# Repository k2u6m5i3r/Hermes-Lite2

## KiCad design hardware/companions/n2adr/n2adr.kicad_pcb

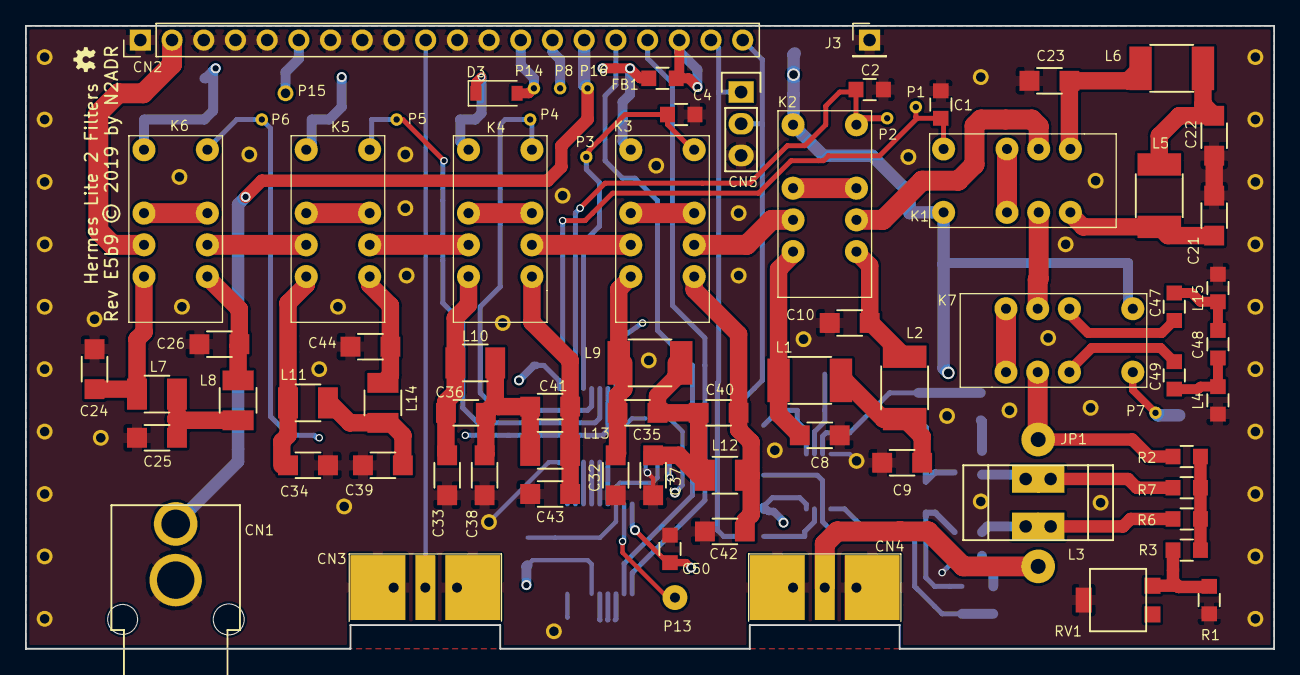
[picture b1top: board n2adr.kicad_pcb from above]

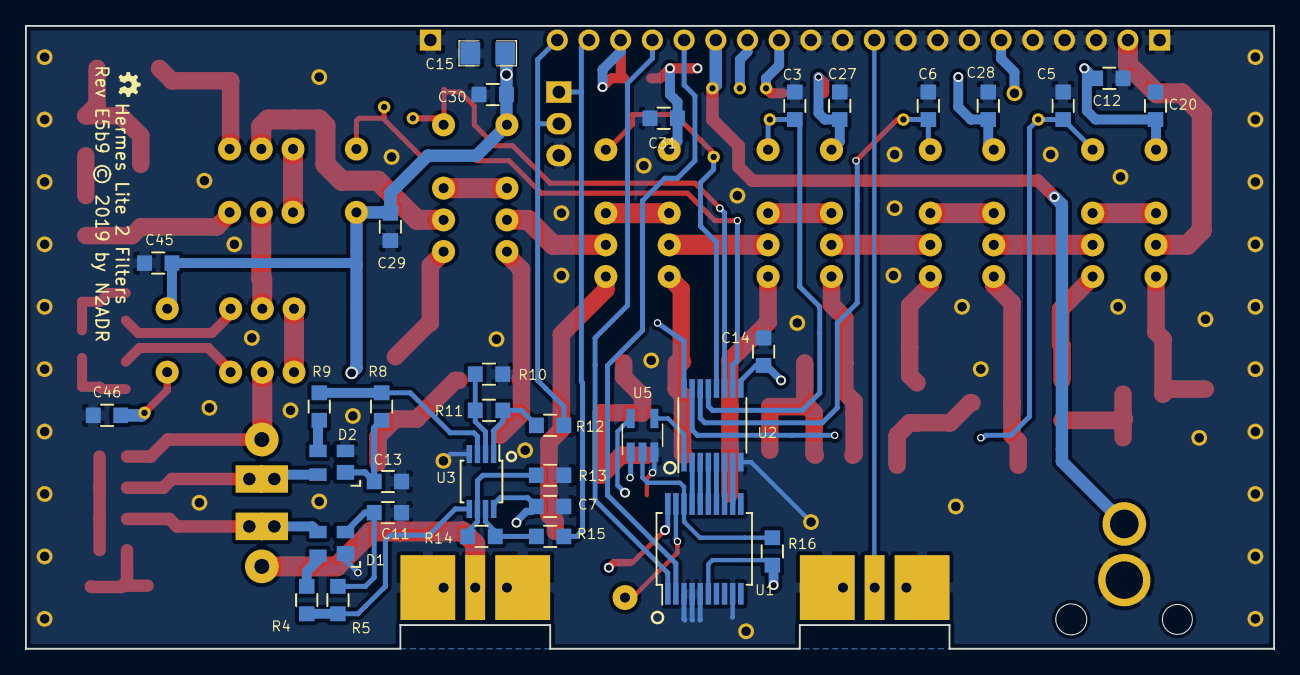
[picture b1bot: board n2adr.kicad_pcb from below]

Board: 4 copper layers, 100.0 x 49.9 mm, 112 parts (34 on the bottom side), 80 nets.

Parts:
C1, C2, C3, C4, C5, C6, C7, C11, C13, C14, C20, C27, C28, C29, C30, C31, C45, C46, C50: 100n; SMD_0805
C8, C10: 1000p; SMD_1206
C9, C21, C23: 1800p; SMD_1206
C12: 22uF; SMD_0805
C15: 100uF; SMD-1206
C22: 3300p; SMD_1206
C24, C26, C33: 150p; SMD_1206
C25, C39: 330p; SMD_1206
C32, C38, C40: 270p; SMD_1206
C34, C44: 180p; SMD_1206
C35: 100p; SMD_1206
C36: 39p; SMD_1206
C37: 560p; SMD_1206
C41, C42: 220p; SMD_1206
C43: 68p; SMD_1206
C47, C49: 1500p; SMD_0805
C48: 680p; SMD_0805
CN1: Audio-Jack-2; PhonoRcaRCJ-04x
CN2: Conn_01x20; Pin_Header_Straight_1x20_Pitch2.54mm
CN3, CN4: SMA; BNCEDGE
CN5: CONN_01X03; Pin_Header_Straight_1x03
D1, D2: BAS40-07; SOT-143
D3: 1N4148; D_SOD-123
FB1: FB; SMD_0805
J3: Conn_01x01; Pin_Header_Straight_1x01_Pitch2.54mm
JP1: 1T; WireConnection_1.20mmDrill
K1, K2, K3, K4, K5, K6, K7: EC2-3NU; RelayDPDT01
L1, L2: 1.8u; SMD_1812
L3: 10T; ToroidT37
L4, L15: 1.8u; SMD_0805
L5, L6: 3.9u; SMD_1812
L7, L8: 220n; SMD_1210
L9: 1000n; SMD_1812
L10: 560n; SMD_1210
L11, L14: 390n; SMD_1210
L12: 680n; SMD_1210
L13: 270n; SMD_1210
P1, P2, P3, P4, P5, P6, P7, P8, P14, P16: TST; WirePad_0.5mm
P13, P15: TST; SolderWirePad_single_0-8mmDrill
R1: 22 1%; SMD_0805
R2, R10, R13: 2K2 1%; SMD_0805
R3: 56 1%; SMD_0805
R4, R5, R8, R9: 4K7; SMD_0805
R6, R7: 18 1%; SMD_0805
R11, R14: 6K2 1%; SMD_0805
R12, R15: 330; SMD_0805
R16: DNI; SMD_0805
RV1: DNI; Trimpot_Bourns_3314G
U1: MCP23008; SSOP-20_5.3x7.2mm_Pitch0.65mm
U2: ULN2003LV; TSSOP-16_4.4x5mm_Pitch0.65mm
U3: AD8692; MSOP-8_3x3mm_Pitch0.65mm
U5: 74LVC1G00; SOT-23-5_HandSoldering

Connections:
+3V3: C7.2, C12.2, C14.2, C15.2, C20.2, C27.2, C28.2, C29.2, C30.2, C31.2, C45.2, C50.2, D3.1, FB1.1, K1.1, K2.1, K3.1, K4.1, K5.1, K6.1, K7.1, R16.1, U1.6, U1.20, U2.9, U3.8, U5.5
Band1: C1.2, K1.8, P1.1, U2.10
Band2: C2.2, K2.8, P2.1, U2.11
Band3: C4.2, K3.8, P3.1, U2.12
Band4: C3.2, K4.8, P4.1, U2.13
Band5: C6.2, K5.8, P5.1, U2.14
Band6: C5.2, K6.8, P6.1, U2.15
Band7: C46.2, K7.8, P7.1, U2.16
FilterOut: JP1.2, K7.6, R2.2
GND: C1.1, C2.1, C3.1, C4.1, C5.1, C6.1, C7.1, C8.1, C9.1, C10.1, C11.2, C12.1, C13.2, C14.1, C15.1, C20.1, C21.2, C22.2, C23.2, C24.1, C25.1, C26.1, C27.1, C28.1, C29.1, C30.1, C31.1, C32.1, C33.1, C34.1, C37.1, C38.1, C39.1, C42.1, C43.1, C44.1, C45.1, C46.1, C50.1, CN1.2, CN2.1, CN2.3, CN2.4, CN2.5, CN2.7, CN2.8, CN2.9, CN2.11, CN2.12, CN3.2, CN4.2, CN5.3, D1.1, D2.2, J3.1, L4.1, L15.1, R1.1, R10.1, R13.1, RV1.2, U1.3, U1.4, U1.5, U1.9, U2.8, U3.4, U5.3
INTTR: CN2.13, D3.2, P14.1, U5.1
unnamed: C8.2, K2.4, L1.1
unnamed: C9.2, L1.2, L2.1
unnamed: C10.2, K2.5, L2.2
unnamed: C11.1, D1.2, R5.2
unnamed: C13.1, D2.1, R8.2
unnamed: C21.1, K1.4, L5.1
unnamed: C22.1, L5.2, L6.1
unnamed: C23.1, K1.5, L6.2
unnamed: C24.2, K6.4, L7.1
unnamed: C25.2, L7.2, L8.1
unnamed: C26.2, K6.5, L8.2
unnamed: C32.2, C35.2, K3.4, L9.1
unnamed: C33.2, C36.2, K4.4, L10.1
unnamed: C34.2, K5.4, L11.1
unnamed: C35.1, C37.2, C40.2, L9.2, L12.1
unnamed: C36.1, C38.2, C41.2, L10.2, L13.1
unnamed: C39.2, L11.2, L14.1
unnamed: C40.1, C42.2, K3.5, L12.2
unnamed: C41.1, C43.2, K4.5, L13.2
unnamed: C44.2, K5.5, L14.2
unnamed: C47.1, C48.2, L15.2
unnamed: C47.2, K7.2
unnamed: C48.1, C49.2, L4.2
unnamed: C49.1, K7.7
unnamed: CN1.1, CN2.15, P16.1
unnamed: CN2.6, P15.1
unnamed: CN2.10, CN3.1
unnamed: CN2.14, P8.1
unnamed: CN2.16, U1.2
unnamed: CN2.17, U1.1
unnamed: CN2.18, FB1.2
unnamed: CN2.19, CN5.1, R15.2
unnamed: CN2.20, CN5.2, R12.2
unnamed: CN4.1, JP1.1
unnamed: D1.3, L3.1, R6.2
unnamed: D1.4, R4.2
unnamed: D2.3, R9.1
unnamed: D2.4, L3.2, R7.1
unnamed: K1.2, K1.7
unnamed: K1.3, K7.3
unnamed: K1.6, K2.6
unnamed: K2.2, K2.7
unnamed: K2.3, K3.6
unnamed: K3.2, K3.7
unnamed: K3.3, K4.6
unnamed: K4.2, K4.7
unnamed: K4.3, K5.6
unnamed: K5.2, K5.7
unnamed: K5.3, K6.6
unnamed: K6.2, K6.7
unnamed: K7.4, K7.5
unnamed: P13.1, U1.19
unnamed: R1.2, R3.1, RV1.1
unnamed: R2.1, R3.2, R6.1, R7.2
unnamed: R4.1, R5.1, U3.5
unnamed: R8.1, R9.2, U3.3
unnamed: R10.2, R11.1, U3.2
unnamed: R11.2, R12.1, U3.1
unnamed: R13.2, R14.1, U3.6
unnamed: R14.2, R15.1, U3.7
unnamed: R16.2, U1.18, U5.2
unnamed: U1.12, U2.7
unnamed: U1.13, U2.6
unnamed: U1.14, U2.5
unnamed: U1.15, U2.4
unnamed: U1.16, U2.3
unnamed: U1.17, U2.2
unnamed: U2.1, U5.4
RFInput: CN2.2, K6.3

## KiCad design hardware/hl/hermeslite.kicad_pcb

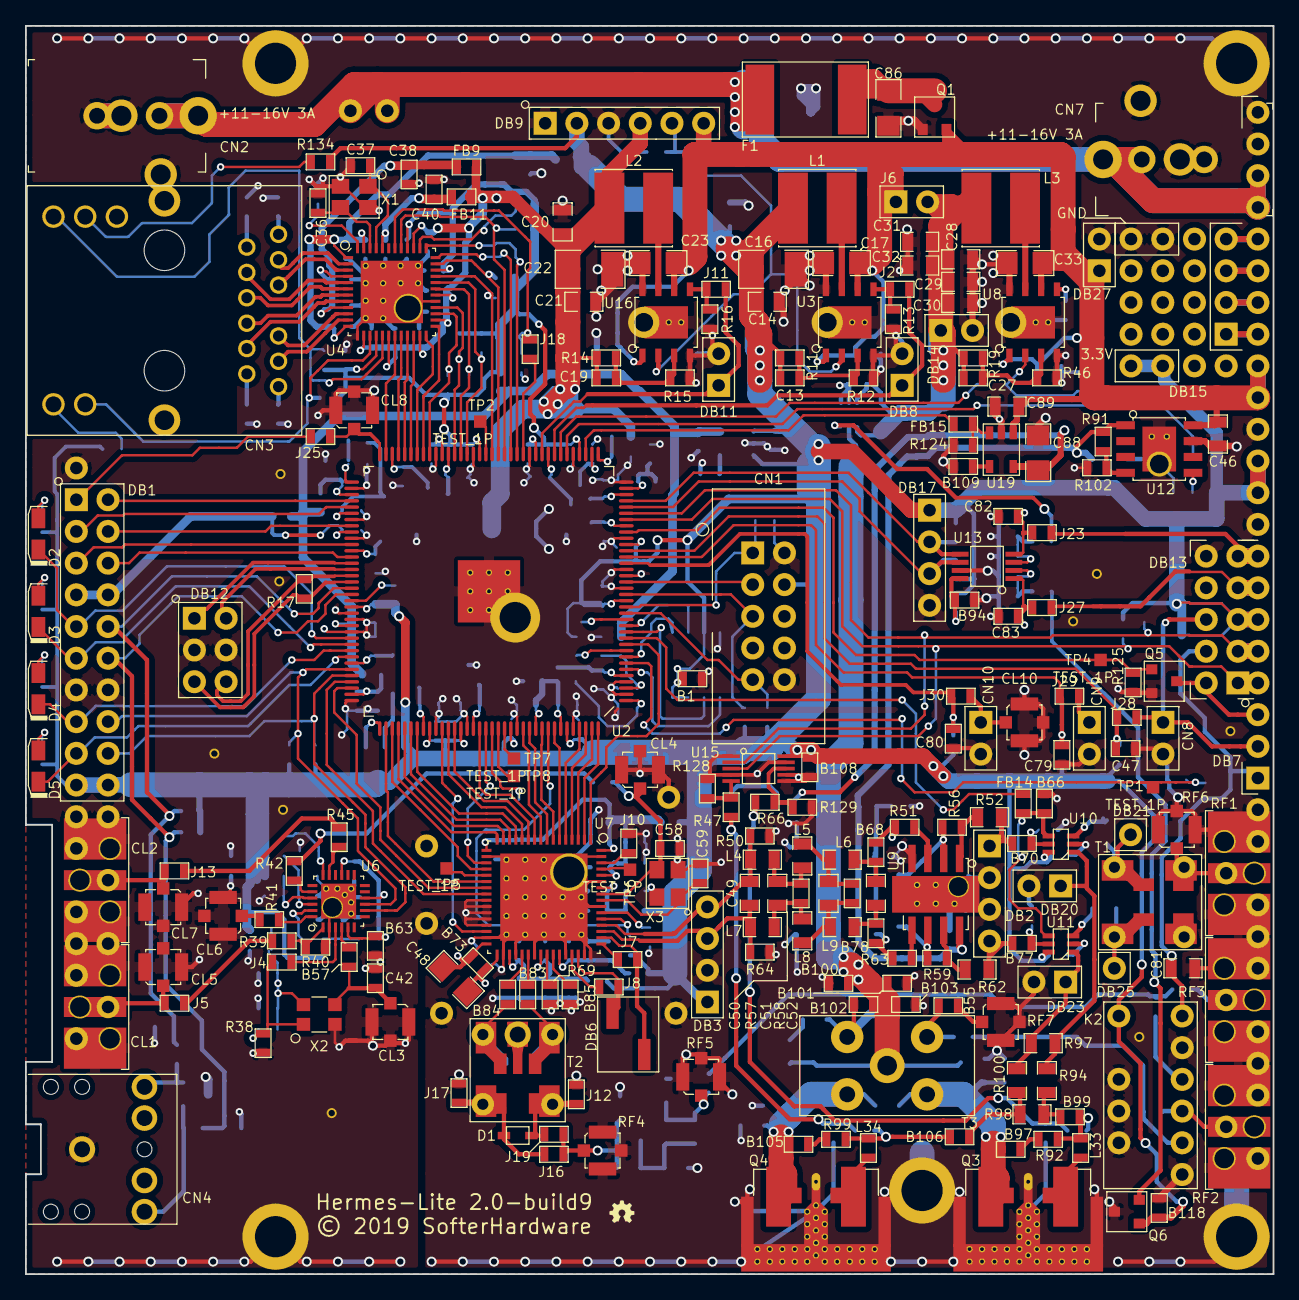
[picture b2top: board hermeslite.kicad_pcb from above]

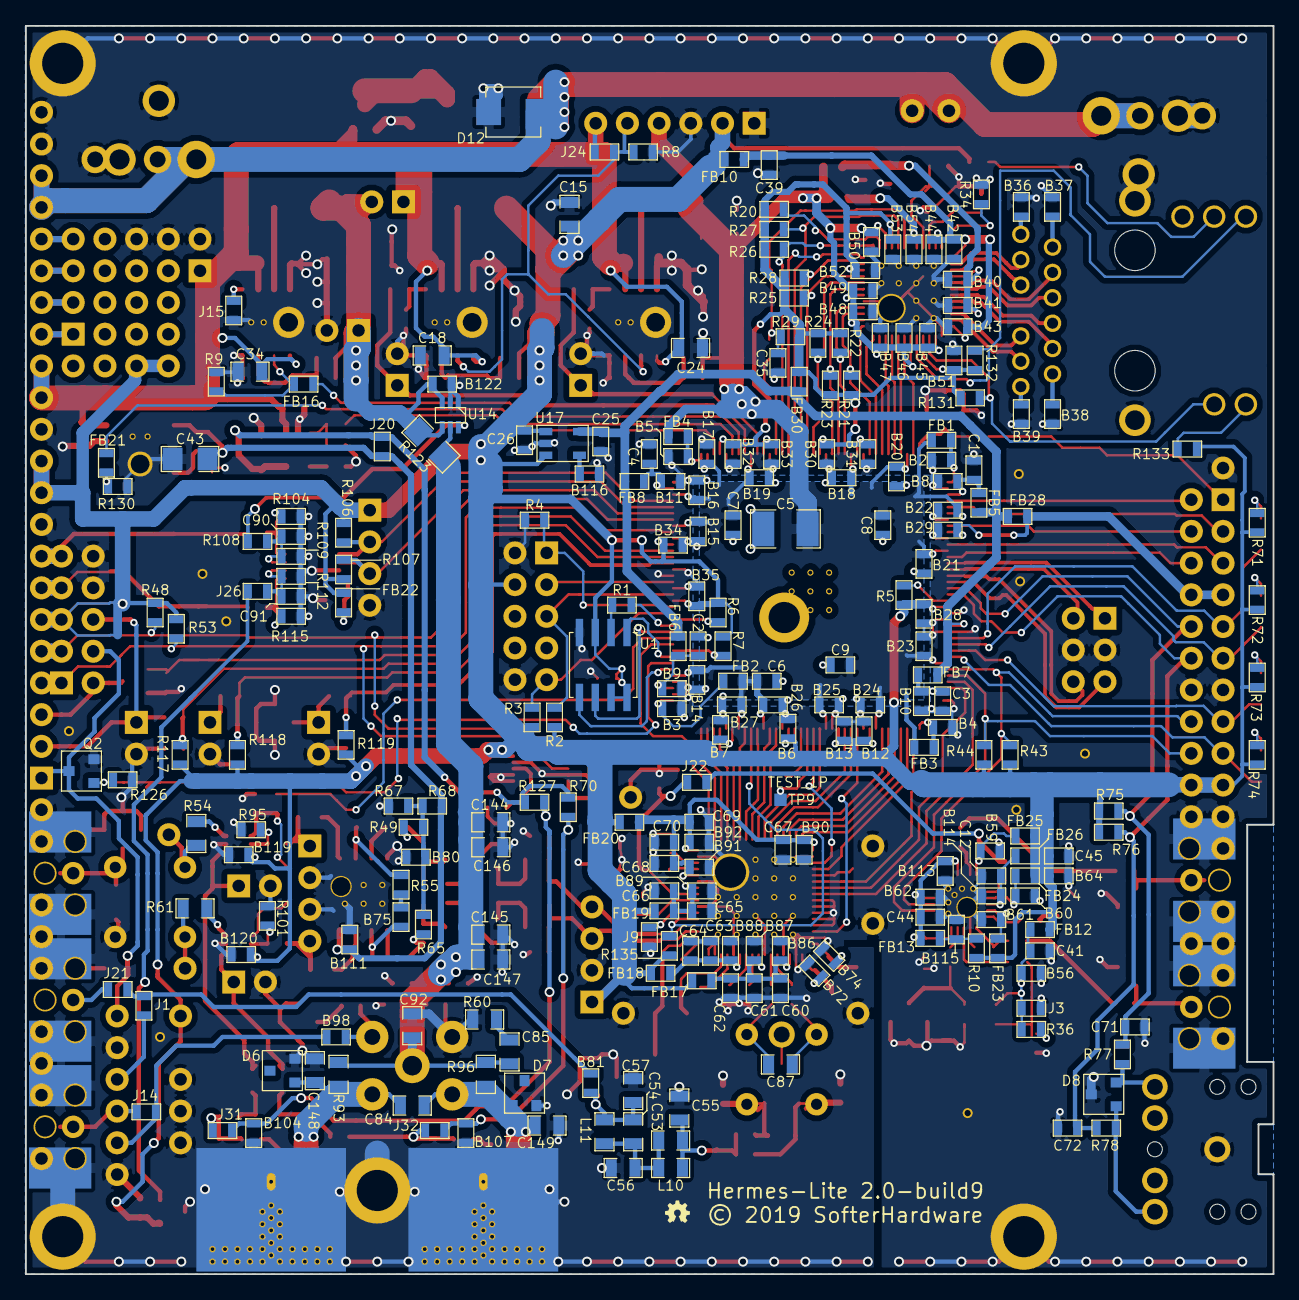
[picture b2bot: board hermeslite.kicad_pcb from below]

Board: 4 copper layers, 99.9 x 100.0 mm, 488 parts (246 on the bottom side), 274 nets.

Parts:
B1, B2, B3, B4, B5, B6, B7, B8, B9, B10, B11, B12, B13, B14, B15, B16, B17, B18, B19, B20, B21, B22, B23, B24, B25, B26, B27, B28, B29, B30, B31, B32, B33, B34, B35, B36, B37, B38, B39, B40, B41, B42, B43, B44, B45, B46, B47, B48, B49, B50, B51, B52, B53, B54, B55, B56, B57, B59, B60, B61, B62, B63, B64, B66, B68, B70, B72, B73, B74, B75, B77, B78, B80, B81, B83, B84, B85, B86, B87, B88, B89, B90, B91, B92, B94, B97, B98, B99, B100, B101, B102, B103, B104, B105, B106, B107, B108, B109, B111, B113, B114, B115, B116, B118, B119, B120, B122: 0.1uF; SMD-0603
C1, C2, C3, C4, C6, C7, C8, C9, C12, C25, C35, C38, C39, C40, C41, C44, C45, C62, C64, C66, C70: 10uF; SMD-0603
C5, C16, C22: 100uF; SMD-1210
C13, C19, C27, C82, C83, C90, C91: 4.7nF; SMD-0603
C14, C15, C20, C21, C28, C29, C30, C31, C32, C92: 22uF; SMD-0805
C17, C23, C33, C43, C48, C86, C88: 10uF; SMD-1206
C18, C24, C34: 4.7uF; SMD-0805
C26, C47, C60, C61, C63, C65, C67, C68, C69, C71, C72, C79, C80: 1uF; SMD-0603
C36, C37, C58, C59: 15pF; SMD-0603
C42: DNI; SMD-0603
C46, C89, C144, C145, C146, C147: 1uF; SMD-0805
C49: 75pF; SMD-0805
C50: 150pF; SMD-0805
C51: 160pF; SMD-0805
C52, C57, C81: 100pF; SMD-0805
C53, C54, C55: 10pF; SMD-0805
C56: 180pF; SMD-0805
C84: 390pF; SMD-0805
C85, C148, C149: 270pF; SMD-0805
C87: 8.2pF; SMD-0805
CL1, CL2: SMA; SMAEDGE_TH_L
CL3, CL4, CL5, CL6, CL7, CL8, CL10: uFL; UFL
CN1: USBBlaster2; USBBLASTER
CN2, CN7: PS; PWRBARREL2
CN3: MagJack; MAGJACK
CN4: STEREO
CN8, CN9, CN10: RFD2b; 2x1
D1: TVS; SOD323
D2, D3, D4, D5: Led_Small; LEDn
D6, D7: DNI; SOT23_3
D8: SM05; SOT23_3
D12: SMBJ18CA; smbj18ca
DB1: IO20; 10x2
DB2, DB3: RFD4d; 4x1
DB6: RFD2b; 2x1smt
DB7: IO22; 22x1
DB8, DB11, DB14, DB20, DB23, DB27: RFD2b; 2x1
DB9: IO6b; 6x1
DB12: IO6b; 3x2
DB13: IO10; 5x2
DB15: IO6b; 4x5
DB17: RFD4b; 4x1
DB21, DB25: DNI; 1x1
F1: 3A@20V; FUSE
FB1, FB2, FB3, FB4, FB5, FB6, FB7, FB8, FB9, FB10, FB11, FB12, FB13, FB14, FB15, FB16, FB17, FB18, FB19, FB20, FB21, FB22, FB23, FB24, FB25, FB26, FB28, FB30: FB; SMD-0603
GT1, GT2, GT3, GT4, GT10, GT11, GT12, GT13, GT14: DNI; GNDTAP
GT5, GT6, GT7, GT8, GT9: DNI; m1d1
J1, J2, J5, J9, J10, J11, J13, J14, J15, J17, J18, J19, J21, J22, J23, J24, J25, J26, J27, J28, J29, J30, J31, J32: JNC; SMD-0603
J3, J4, J7, J8, J12, J16, J20: JNO; SMD-0603
J6: RFD2b; 2x1
K2: NA3WK-K; DPDT_GND
L1, L3: 3.3uH; GENERICPSL
L2: 2.2uH; GENERICPSL
L4, L7: 240nH; SMD-0805
L5, L6, L8, L9: 270nH; SMD-0805
L10, L11: 330nH; SMD-0805
L33, L34: 0nH; SMD-0603
MH1, MH2, MH3, MH4, MH5: DNI; m3
MH6, MH7, MH8: DNI; m1d1
Q1: DMP3099L; SOT23_3
Q2, Q5: NUD3124; SOT23_3
Q3, Q4: LDMOS; COMBORFGNDnohole
Q6: MCP9700; SOT23_3
R1, R41, R42, R45, R50, R64: 33; SMD-0603
R2, R3, R4, R5, R6, R7, R8, R9, R13, R14, R16, R21, R22, R23, R24, R25, R27, R28, R29, R128, R129, R131, R132: 10K; SMD-0603
R10: 2.2; SMD-0603
R11: 35.7K; SMD-0603
R12, R91: 11.5K; SMD-0603
R15: 20K; SMD-0603
R17, R77, R78: 100; SMD-0603
R19: 16.2K; SMD-0603
R20, R26, R49, R65, R75, R76: 2.2K; SMD-0603
R34: 12.1K; SMD-0603
R36, R38: DNI; SMD-0603
R39: 130; SMD-0603
R40: 75; SMD-0603
R43, R44, R48, R53, R95, R101, R106, R107, R117, R118, R119, R124, R125, R126, R130, R135: 4.7K; SMD-0603
R46: 1.8K; SMD-0603
R47, R66: 9.1K; SMD-0603
R51, R63: 22; SMD-0603
R52, R54, R61, R62, R94, R100: 12; SMD-0805
R55: 120; SMD-0603
R56, R59: 330; SMD-0603
R57, R58, R67, R68, R71, R72, R73, R74, R104, R109, R112, R115: 1K; SMD-0603
R60, R93, R96, R97, R98: 1K; SMD-0805
R69, R102: 1.6K; SMD-0603
R70, R127: 27K; SMD-0603
R92, R99, R108, R133, R134: 270; SMD-0603
R123: 0.04; SMD-1206
RF1, RF2: SMA/BNC; SMAEDGE_TH_R
RF3: SMA; SMAEDGE_TH_R
RF4, RF5, RF6, RF7: uFL; UFL
T1: 1:1 Z; TRANSFSMT4
T2: 8:1 Z; TRANSFSMT
T3: 4:1 Z; BN202V
TP1, TP2, TP4, TP5, TP6, TP7, TP8, TP9: TEST_1P; TP
U1: EEPROM; SOIC-8
U2: FPGA; CYCLONEIV
U3, U8, U16: ST1S10
U4: KSZ9031RN; KSZ9031
U6: 5P49V5923; IDTVERSA
U7: AD9866BCPZ; AD9866
U9: OPA2677
U10, U11: PE4259
U12: AP2204; ap2204
U13: MAX11613
U14: INA199A1DC; PE4259
U15: MCP4662; SOIC-10
U17: TPS730; SOT23
U19: LP2985; SOT23
X1: 25MHz; XTAL
X2: 38.4MHz; SMALLOSC
X3: 38.4MHz; XTAL

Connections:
+1V2: B14.1, B15.1, B16.1, B17.1, B18.1, B19.1, B20.1, B21.1, B22.1, B23.1, B24.1, B25.1, B26.1, B27.1, B45.1, B46.1, B47.1, B48.1, B49.1, B50.1, C5.2, C6.2, C7.2, C8.2, C9.2, C19.1, C20.1, C21.1, C22.1, DB9.4, FB1.1, FB2.1, FB3.1, FB4.1, FB9.1, FB11.1, L2.2, R14.1, U2.5, U2.29, U2.34, U2.38, U2.45, U2.61, U2.70, U2.78, U2.84, U2.102, U2.116, U2.124, U2.134, U2.138, U4.14, U4.18, U4.23, U4.26, U4.30, U4.39
+2V5: C25.1, FB5.1, FB6.1, FB7.1, FB8.1, FB28.1, FB30.1, U2.96, U17.5
+3V3: B1.1, B6.1, B7.1, B12.1, B13.1, B28.1, B34.1, B35.1, B64.1, B108.1, B118.1, B119.1, B120.1, C13.1, C14.1, C15.1, C16.1, C26.1, C45.1, CN1.4, DB1.19, DB1.20, DB3.1, DB7.6, DB7.10, DB7.11, DB9.2, DB13.5, DB15.5, DB17.1, FB10.2, FB12.2, FB17.2, FB18.1, FB19.1, FB20.2, FB22.1, FB23.2, FB24.2, FB25.2, FB26.2, K2.1, L1.2, Q6.1, R2.2, R3.2, R5.2, R6.2, R7.2, R10.1, R11.1, R43.1, R44.1, R48.2, R53.2, R71.2, R72.2, R73.2, R74.2, R75.2, R76.2, R106.2, R107.2, R117.2, R118.2, R119.2, R133.2, R134.2, R135.2, U1.3, U1.7, U1.8, U2.17, U2.26, U2.93, U2.117, U2.122, U2.130, U2.139, U10.6, U11.6, U15.10, U17.1, U17.3
+VBIAS: C88.1, J20.1, R70.2, R127.2, U19.5
+VOP: B111.2, C43.1, J20.2, R68.2, R91.1, U9.8, U12.1
+VPA: B122.1, C27.1, C28.1, C29.1, C30.1, C31.1, C32.1, DB14.1, J6.2, L3.2, R19.1, R123.1, U14.3, U14.4
/Ethernet/RXD0: R24.2, U2.58, U4.32
/Ethernet/RXD1: R23.2, U2.59, U4.31
/Ethernet/RXD2: R22.2, U2.60, U4.28
/Ethernet/RXD3: R21.2, U2.64, U4.27
/Ethernet/TXD0: U2.71, U4.19
/Ethernet/TXD1: U2.69, U4.20
/Ethernet/TXD2: U2.68, U4.21
/Ethernet/TXD3: U2.67, U4.22
/Input Output/AIN1: DB7.7, DB13.7, J27.2
/Input Output/AIN2: DB7.8, DB13.9, J23.2
/Input Output/CN8: CN8.1, DB7.2, DB13.6, J28.1
/Input Output/SPR1: DB7.15, DB15.1
/Input Output/SPR2: DB7.16, DB15.2
/Input Output/SPR3: DB7.17, DB15.3
/Input Output/SPR4: DB7.18, DB15.4
/PA/bias0: B104.2, J31.2, R66.2, R127.1
/PA/bias1: B107.2, J32.2, R47.2, R70.1
/Power and FPGA/enpwr: DB9.5, J24.2, R8.1, U3.2, U16.2
/RF Frontend/Vop/2: B80.2, R49.1, R65.2, R67.2, R68.1
EXTTR: DB7.3, DB13.2, Q5.3
GND: B1.2, B2.2, B3.2, B4.2, B5.2, B6.2, B7.2, B8.2, B9.2, B10.2, B11.2, B12.2, B13.2, B14.2, B15.2, B16.2, B17.2, B18.2, B19.2, B20.2, B21.2, B22.2, B23.2, B24.2, B25.2, B26.2, B27.2, B28.2, B29.2, B30.2, B31.2, B32.2, B33.2, B34.2, B35.2, B36.2, B37.2, B38.2, B39.2, B40.2, B41.2, B42.2, B43.2, B44.2, B45.2, B46.2, B47.2, B48.2, B49.2, B50.2, B51.2, B52.2, B53.2, B54.2, B56.2, B59.2, B60.2, B61.2, B62.2, B63.2, B64.2, B66.1, B72.2, B74.2, B80.1, B85.2, B86.2, B87.2, B88.2, B89.2, B90.2, B91.2, B92.2, B94.2, B100.1, B101.1, B102.1, B103.1, B104.1, B107.1, B108.2, B109.2, B111.1, B113.2, B114.2, B115.2, B116.2, B118.2, B119.2, B120.2, B122.2, C1.2, C2.2, C3.2, C4.2, C5.1, C6.1, C7.1, C8.1, C9.1, C12.2, C14.2, C15.2, C16.2, C17.2, C18.2, C20.2, C21.2, C22.2, C23.2, C24.2, C25.2, C26.2, C28.2, C29.2, C30.2, C31.2, C32.2, C33.2, C34.2, C35.2, C36.2, C37.2, C38.2, C39.2, C40.2, C41.2, C42.1, C43.2, C44.2, C45.2, C46.2, C47.2, C55.2, C56.2, C57.2, C58.2, C59.2, C60.2, C61.2, C62.2, C63.2, C64.2, C65.2, C66.2, C67.2, C68.2, C69.2, C70.2, C71.2, C72.2, C79.2, C80.2, C81.2, C82.2, C83.2, C86.2, C88.2, C89.2, C90.2, C91.2, C92.2, C144.2, C145.2, C146.2, C147.2, C148.2, C149.2, CL1.2, CL2.2, CL3.2, CL4.2, CL5.2, CL6.2, CL7.2, CL8.2, CL10.2, CN1.2, CN1.10, CN2.2, CN3.18, CN4.1, CN7.2, CN8.2, CN9.2, CN10.2, D6.2, D7.2, D8.3, D12.2, DB1.13, DB1.14, DB2.2, DB2.3, DB3.2, DB7.9, DB7.12, DB7.21, DB7.22, DB8.2, DB9.1, DB9.3, DB11.2, DB12.3, DB12.4, DB13.8, DB13.10, DB14.2, DB15.6, DB17.4, DB20.2, DB23.2, DB27.2, GT1.1, GT2.1, GT3.1, GT4.1, GT5.1, GT6.1, GT7.1, GT8.1, GT9.1, GT10.1, GT11.1, GT12.1, GT13.1, GT14.1, J3.2, J9.1, J10.1, J12.2, J15.1, J17.1, K2.3, K2.4, K2.5, K2.7, K2.11, MH1.1, MH2.1, MH3.1, MH4.1, MH5.1, MH6.1, Q1.1, Q2.2, Q3.2, Q4.2, Q5.2, Q6.3, R4.2, R8.2, R9.2, R12.2, R13.1, R15.2, R16.1, R34.2, R38.2, R40.2, R46.2, R50.2, R60.1, R64.1, R67.1, R69.1, R95.2, R101.1, R102.1, R104.1, R109.1, R112.1, R115.1, R124.1, R125.1, R126.1, R128.1, R129.1, R130.1, RF1.2, RF2.2, RF3.2, RF4.2, RF5.2, RF6.2, RF7.2, T1.3, T3.4, U1.4, U2.2, U2.4, U2.19, U2.21, U2.22, U2.27, U2.36, U2.41, U2.48, U2.57, U2.63, U2.74, U2.79, U2.82, U2.94, U2.95, U2.97, U2.108, U2.118, U2.123, U2.131, U2.140, U2.145, U3.4, U3.8, U3.9, U4.13, U4.29, U4.49, U6.2, U6.25, U7.18, U7.25, U7.26, U7.27, U7.28, U7.29, U7.31, U7.34, U7.36, U7.39, U7.44, U7.47, U7.48, U7.55, U7.59, U7.63, U7.65, U8.4, U8.8, U8.9, U9.4, U10.2, U11.2, U12.7, U13.7, U14.1, U14.2, U15.1, U15.4, U15.6, U15.7, U15.9, U16.4, U16.8, U16.9, U17.2, U19.2, X1.3, X2.2, X3.3
INTTR: C81.1, DB7.1, DB13.4, K2.12, Q2.3
unnamed: B2.1, FB1.2, U2.73
unnamed: B3.1, FB2.2, U2.1
unnamed: B4.1, FB3.2, U2.109
unnamed: B5.1, FB4.2, U2.37
unnamed: B8.1, C1.1, FB5.2, U2.75
unnamed: B9.1, C2.1, FB6.2, U2.3
unnamed: B10.1, C3.1, FB7.2, U2.107
unnamed: B11.1, C4.1, FB8.2, U2.35
unnamed: B36.1, CN3.12
unnamed: B37.1, CN3.6
unnamed: B38.1, CN3.1
unnamed: B39.1, CN3.7
unnamed: B40.1, B41.1, C38.1, FB9.2, U4.4, U4.9
unnamed: B42.1, B43.1, B44.1, C39.1, FB10.1, U4.1, U4.12, U4.47
unnamed: B54.1, C40.1, FB11.2, U4.44
unnamed: B55.1, B98.2, T3.5
unnamed: B55.2, RF7.1
unnamed: B56.1, C41.1, FB12.1, J3.1, R36.1, X2.4
unnamed: B57.1, C42.2, CL3.1, X2.3
unnamed: B57.2, U6.4
unnamed: B59.1, FB25.1, U6.18
unnamed: B60.1, FB24.1, U6.21
unnamed: B61.1, FB23.1, U6.23
unnamed: B66.2, FB14.1, U10.4, U11.4
unnamed: B68.1, R49.2, R51.2
unnamed: B68.2, C52.1, L6.2
unnamed: B70.1, R95.1, U10.5
unnamed: B70.2, DB2.1, R52.1
unnamed: B72.1, B73.1, C48.1, U7.33
unnamed: B73.2, B74.1, C48.2, U7.32
unnamed: B75.1, R59.2, U9.6
unnamed: B75.2, R55.1
unnamed: B77.1, R101.2, U11.5
unnamed: B77.2, DB2.4, R62.1
unnamed: B78.1, R63.2, R65.1
unnamed: B78.2, C52.2, L9.1
unnamed: B81.1, J1.1, J21.1
unnamed: B81.2, C54.1, C57.1, L11.2, RF5.1
unnamed: B83.1, C87.1, T2.1
unnamed: B83.2, U7.38
unnamed: B84.1, C87.2, T2.3
unnamed: B84.2, U7.37
unnamed: B85.1, U7.42
unnamed: B86.1, B87.1, C60.1, C61.1, C62.1, FB17.1, U7.35, U7.40
unnamed: B88.1, C63.1, C64.1, FB18.2, U7.43
unnamed: B89.1, C65.1, C66.1, FB19.2, U7.58
unnamed: B90.1, B91.1, B92.1, C67.1, C68.1, C69.1, C70.1, FB20.1, U7.17, U7.60, U7.64
unnamed: B94.1, FB22.2, U13.8
unnamed: B97.1, C84.1, C148.1, D6.1, Q3.3, R93.2, T3.1
unnamed: B97.2, R92.1
unnamed: B98.1, J14.2, K2.8
unnamed: B99.1, J31.1, L33.1, R92.2
unnamed: B99.2, R94.1, R98.2
unnamed: B100.2, B101.2, B102.2, B103.2, C85.2, C92.1, C144.1, C145.1, C146.1, C147.1, R93.1, R96.2, R123.2, T3.2, U14.5
unnamed: B105.1, C84.2, C149.1, D7.1, Q4.3, R96.1, T3.3
unnamed: B105.2, R99.1
unnamed: B106.1, J32.1, L34.1, R99.2
unnamed: B106.2, R98.1, R100.1
unnamed: B109.1, U19.4
unnamed: B62.1, B63.1, B113.1, C44.1, FB13.1, U6.5, U6.10, U6.15
unnamed: B114.1, C12.1, FB26.1, U6.22
unnamed: B115.1, FB13.2, R10.2
unnamed: B116.1, U17.4
unnamed: C13.2, R11.2, R12.1, U3.3
unnamed: C19.2, R14.2, R15.1, U16.3
unnamed: C27.2, R19.2, R46.1, U8.3
unnamed: C35.1, J18.1, R29.1, U4.42
unnamed: C36.1, U4.46, X1.2
unnamed: C37.1, U4.45, X1.1
unnamed: C47.1, J28.2, R117.1, U2.25
unnamed: C49.1, DB3.4, L4.1, R50.1, U7.52
unnamed: C49.2, DB3.3, L7.2, R64.2, U7.51
unnamed: C50.1, L4.2, L5.1, R57.2
unnamed: C50.2, L7.1, L8.2, R57.1
unnamed: C51.1, L5.2, L6.1, R58.2
unnamed: C51.2, L8.1, L9.2, R58.1
unnamed: C53.1, C54.2, C56.1, L10.2, L11.1
unnamed: C53.2, C55.1, J16.1, J19.2, L10.1, RF4.1
unnamed: C58.1, CL4.1, J22.2, U7.57, X3.2
unnamed: C59.1, U7.56, X3.1
unnamed: C71.1, DB1.10, R75.1, R77.1, U2.90
unnamed: C72.1, DB1.12, R76.1, R78.1, U2.91
unnamed: C79.1, J29.2, R118.1, U2.24
unnamed: C80.1, J30.2, R119.1, U2.23
unnamed: C82.1, J23.1, R104.2, U13.4
unnamed: C83.1, J27.1, R115.2, U13.1
unnamed: C85.1, R60.2
unnamed: C86.1, F1.2, Q1.3
unnamed: C90.1, R108.1, R109.2, U13.3
unnamed: C91.1, J26.1, R112.2, U13.2
unnamed: CL1.1, CL5.1, J5.1
unnamed: CL2.1, CL7.1, J13.2
unnamed: CL6.1, R41.1
unnamed: CL8.1, J25.1, U2.72
unnamed: CL10.1, CN10.1, J30.1
unnamed: CN1.1, R4.1, U2.16
unnamed: CN1.3, U2.20
unnamed: CN1.5, R2.1, U2.18
unnamed: CN1.9, R3.1, U2.15
unnamed: CN3.2, U4.8
unnamed: CN3.3, U4.7
unnamed: CN3.4, U4.6
unnamed: CN3.5, U4.5
unnamed: CN3.8, U4.11
unnamed: CN3.9, U4.10
unnamed: CN3.10, U4.3
unnamed: CN3.11, U4.2
unnamed: CN3.13, R131.2, U4.15
unnamed: CN3.14, R133.1
unnamed: CN3.16, R134.1
unnamed: CN3.17, R132.2, U4.17
unnamed: CN4.2, D8.1, R78.2
unnamed: CN4.3, D8.2, R77.2
unnamed: CN9.1, J29.1
unnamed: D1.1, J16.2, J17.2, T2.4
unnamed: D1.2, J12.1, J19.1, T2.5
unnamed: D2.1, DB1.9, U2.98
unnamed: D2.2, R71.1
unnamed: D3.1, DB1.11, U2.99
unnamed: D3.2, R72.1
unnamed: D4.1, DB1.15, U2.100
unnamed: D4.2, R73.1
unnamed: D5.1, DB1.17, U2.101
unnamed: D5.2, R74.1
unnamed: DB1.1, J25.2
unnamed: DB1.2, U2.76
unnamed: DB1.3, U2.77
unnamed: DB1.4, U2.80
unnamed: DB1.5, U2.83
unnamed: DB1.6, U2.85
unnamed: DB6.1, J8.1, U7.46
unnamed: DB6.2, J7.1, U7.50
unnamed: DB8.1, J2.2, U2.44
unnamed: DB11.1, J11.2, U2.46
unnamed: DB12.1, U2.86
unnamed: DB12.2, U2.87
unnamed: DB12.5, R17.2, U2.89
unnamed: DB12.6, R17.1, U2.88
unnamed: DB17.2, R106.1, U2.33, U13.5
unnamed: DB17.3, R107.1, U2.32, U13.6
unnamed: DB21.1, R54.1, T1.1
unnamed: DB25.1, R61.1, T1.2
unnamed: FB14.2, U2.11
unnamed: FB15.1, U2.39
unnamed: FB15.2, R124.2, U19.3
unnamed: FB16.1, U2.43
unnamed: FB16.2, R9.1, U8.2
unnamed: FB21.1, U2.42
unnamed: FB21.2, R130.2, U12.5
unnamed: J2.1, R13.2, U3.5
unnamed: J4.1, R36.2, R38.1, X2.1
unnamed: J4.2, U6.3
unnamed: J5.2, R39.2
unnamed: J7.2, U7.49
unnamed: J8.2, U7.45
unnamed: J9.2, U7.54
unnamed: J10.2, U7.62
unnamed: J11.1, R16.2, U16.5
unnamed: J13.1, R45.1
unnamed: J14.1, K2.9, RF2.1
unnamed: J15.2, U8.5
unnamed: J18.2, U2.49
unnamed: J21.2, RF3.1
unnamed: L1.1, U3.7
unnamed: L2.1, U16.7
unnamed: L3.1, U8.7
unnamed: L33.2, Q3.1
unnamed: L34.2, Q4.1
unnamed: Q2.1, R126.2, TP1.1, U2.7
unnamed: Q5.1, R125.2, TP4.1, U2.28
unnamed: R1.1, U1.2
unnamed: R1.2, U2.13
unnamed: R5.1, U2.92
unnamed: R6.1, U2.14
unnamed: R7.1, U2.9
unnamed: R20.2, U4.38
unnamed: R25.2, U2.54, U4.33
unnamed: R26.2, U2.50, U4.37
unnamed: R27.1, U2.52, U4.41
unnamed: R28.1, U2.53, U4.35
unnamed: R34.1, U4.48
unnamed: R39.1, R40.1, U6.1
unnamed: R41.2, U6.24
unnamed: R42.2, U6.20
unnamed: R45.2, U6.17
unnamed: R51.1, U9.3
unnamed: R52.2, R56.1, U9.1
unnamed: R54.2, U10.3
unnamed: R55.2, R56.2, U9.2
unnamed: R59.1, R62.2, U9.7
unnamed: R61.2, U11.3
unnamed: R63.1, U9.5
unnamed: R69.2, U7.41
unnamed: R91.2, R102.2, U12.4
unnamed: R47.1, R128.2, U15.5
unnamed: R66.1, R129.2, U15.8
unnamed: R135.1, U2.136, U7.53
unnamed: RF1.1, RF6.1, T1.4
unnamed: TP2.1, U2.55
unnamed: TP5.1, U7.21
unnamed: TP6.1, U7.61
unnamed: TP7.1, U2.129
unnamed: TP8.1, U2.128
unnamed: TP9.1, U2.127
unnamed: U1.1, U2.8
unnamed: U1.5, U2.6
unnamed: U1.6, U2.12
unnamed: U2.10, U7.1
unnamed: U2.51, U4.36
unnamed: U2.65, U4.25
unnamed: U2.66, U4.24
unnamed: U2.105, U7.24
unnamed: U2.106, U7.23
unnamed: U2.110, U7.22
unnamed: U2.111, U7.20
unnamed: U2.112, U7.16
unnamed: U2.113, U7.15
unnamed: U2.114, U7.14
unnamed: U2.115, U7.13
unnamed: U2.119, U7.30
unnamed: U2.120, U7.12
unnamed: U2.121, U7.11
unnamed: U2.125, U7.10
unnamed: U2.126, U7.19
unnamed: U2.132, U7.9
unnamed: U2.133, U7.8
unnamed: U2.135, U7.7
unnamed: U2.137, U7.6
unnamed: U2.141, U7.5
unnamed: U2.142, U7.4
unnamed: U2.143, U7.3
unnamed: U2.144, U7.2
PATRRX: J1.2, K2.10
RFFE_CLK: J22.1, R42.1
SCL1: DB1.16, R43.2, U2.103, U6.9
SCL2: DB7.5, DB13.3, R48.1, U2.31, U15.2
SDA1: DB1.18, R44.2, U2.104, U6.8
SDA2: DB7.4, DB13.1, R53.1, U2.30, U15.3
TXPAn: DB23.1, R97.1, R100.2, U11.1
TXPAp: DB20.1, R94.2, R97.2, U10.1
VEXT: CN2.1, CN7.1, D12.1, DB7.19, DB7.20, F1.1, MH7.1, MH8.1
VSUP: C17.1, C18.1, C23.1, C24.1, C33.1, C34.1, C46.1, C89.1, DB7.13, DB7.14, DB9.6, DB27.1, J6.1, J24.1, Q1.2, U3.1, U3.6, U8.1, U8.6, U12.8, U16.1, U16.6, U19.1
Veth: B30.1, B31.1, B32.1, B33.1, B51.1, B52.1, B53.1, FB30.2, R20.1, R21.1, R22.1, R23.1, R24.1, R25.1, R26.1, R27.2, R28.2, R29.2, R131.1, R132.1, U2.40, U2.47, U2.56, U2.62, U4.16, U4.34, U4.40
Vipa: R108.2, U14.6
Vlvds: B29.1, DB1.7, DB1.8, FB28.2, U2.81
Vtemp: J26.2, Q6.2

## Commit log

2023-01-30 add: ibom
2023-01-30 add: ibom pream

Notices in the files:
hardware/companions/n2adr/n2adr.kicad_pcb:
Rev E5b9 © 2019 by N2ADR
hardware/hl/hermeslite.kicad_pcb:
© 2019 SofterHardware
